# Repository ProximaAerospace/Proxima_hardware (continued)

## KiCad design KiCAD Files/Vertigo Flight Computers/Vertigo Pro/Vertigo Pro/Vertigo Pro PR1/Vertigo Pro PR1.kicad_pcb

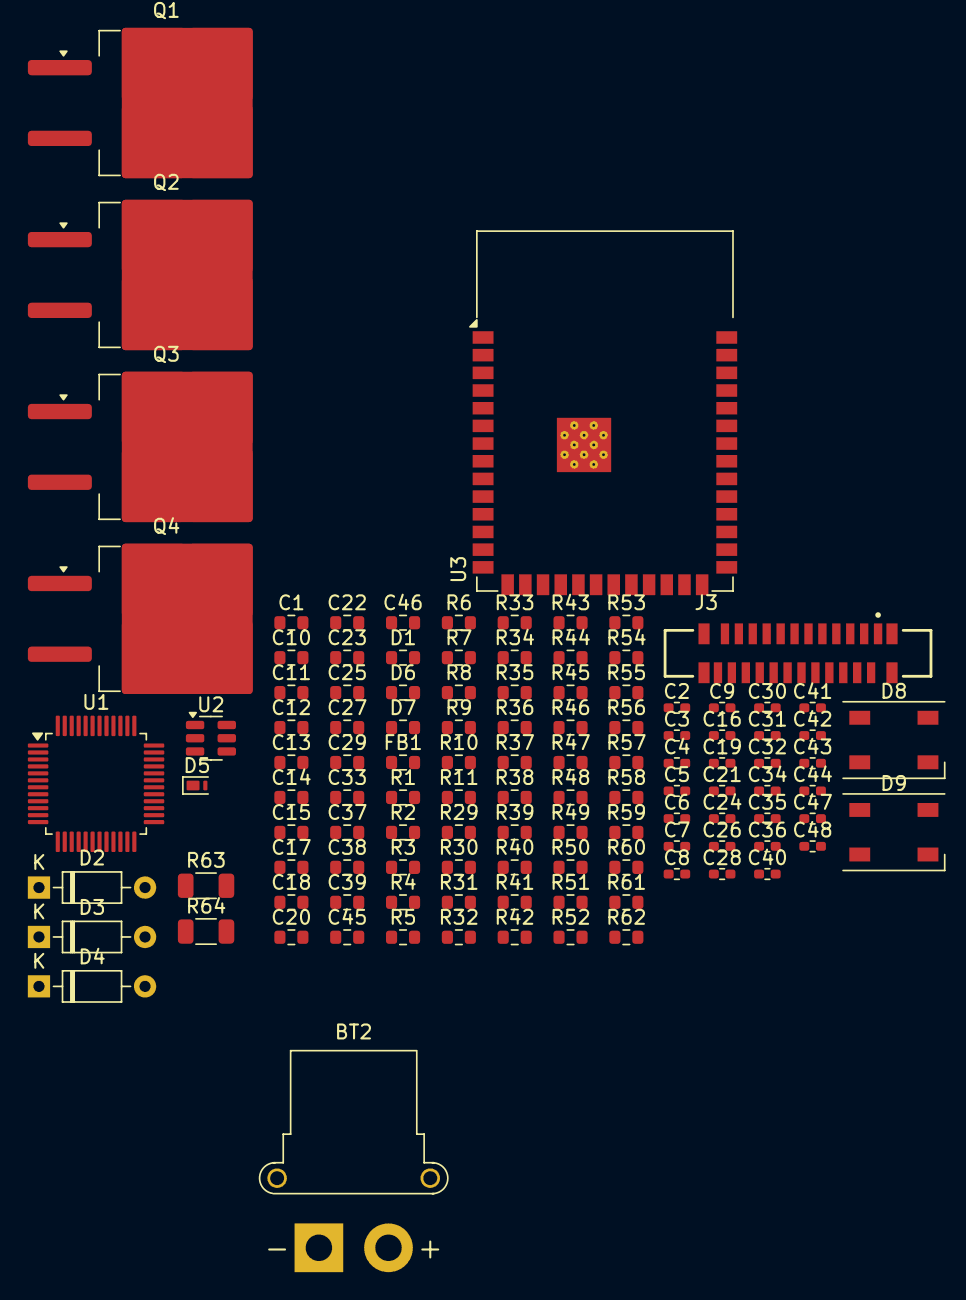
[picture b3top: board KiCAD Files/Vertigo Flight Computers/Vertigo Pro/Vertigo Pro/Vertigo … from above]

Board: 4 copper layers, 114 parts (0 on the bottom side), 68 nets, no tracks yet.

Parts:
BT2: 3S LiPo; AMASS_XT30PW-F_1x02_P2.50mm_Horizontal
C1, C12, C17, C23, C25, C27, C29: 10uF; R_0603_1608Metric
C2, C4, C6, C7, C8, C35, C36: 100nF; R_0402_1005Metric_Pad0.72x0.64mm_HandSolder
C3, C5: 10pF; R_0402_1005Metric_Pad0.72x0.64mm_HandSolder
C9, C31: 10nF; R_0402_1005Metric_Pad0.72x0.64mm_HandSolder
C10, C11, C39: 1uF; R_0603_1608Metric
C13: 100nF; R_0603_1608Metric
C14, C15: 22uF; R_0603_1608Metric
C16, C19, C21, C24, C26, C28, C30, C32, C34, C40, C41, C43, C44, C47: 0.1uF; R_0402_1005Metric_Pad0.72x0.64mm_HandSolder
C18, C20, C22, C45, C46: 4.7uF; R_0603_1608Metric
C33, C37, C38: 2.2uF; R_0603_1608Metric
C42, C48: 0.47uF; R_0402_1005Metric_Pad0.72x0.64mm_HandSolder
D1, D6: LED; R_0603_1608Metric
D2, D3, D4: 1N4148; D_DO-35_SOD27_P7.62mm_Horizontal
D5: uClamp0571P; Nexperia_DSN1608-2_1.6x0.8mm
D7: D; R_0603_1608Metric
D8, D9: SK6812; LED_SK6812_PLCC4_5.0x5.0mm_P3.2mm
FB1: 120R; R_0603_1608Metric
J3: FFC2A32-24-T; GCT_FFC2A32-24-T
Q1, Q2, Q3, Q4: IRF530SPBF; TO-263-2
R1, R9, R10, R29, R30, R31, R32, R33: 10K; R_0603_1608Metric
R2, R3, R44: 22R; R_0603_1608Metric
R4, R5: 5.1k; R_0603_1608Metric
R6: 3k; R_0603_1608Metric
R7, R8: 1K; R_0603_1608Metric
R11, R43, R45, R46, R49, R51, R52, R55, R56, R57, R58: 1k; R_0603_1608Metric
R34: 18.2k; R_0603_1608Metric
R35, R37, R39, R41: 5k; R_0603_1608Metric
R36: 64.4k; R_0603_1608Metric
R38: 23.7k; R_0603_1608Metric
R40: 10.2k; R_0603_1608Metric
R42: 21.5k; R_0603_1608Metric
R47, R53, R59, R60: 10k; R_0603_1608Metric
R48: 1.5k; R_0603_1608Metric
R50, R54, R61, R62: 3.44k; R_0603_1608Metric
R63, R64: 470R; R_1206_3216Metric
U1: STM32F103C8Tx; LQFP-48_7x7mm_P0.5mm
U2: AP63203WU; TSOT-23-6
U3: ESP32-S3-WROOM-1

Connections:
+3.3V: C1.1, C4.1, C6.1, C7.1, C8.1, C11.1, C14.1, C15.1, C16.2, C17.2, C23.2, C24.1, C27.2, C28.1, C31.2, C32.2, C33.2, C35.2, C36.1, C37.1, C38.2, FB1.2, R7.2, R29.2, R30.2, R31.2, R32.2, R33.2, U1.1 (VBAT), U1.24 (VDD), U1.36 (VDD), U1.48 (VDD), U2.1 (FB), U3.2 (3V3)
+3.3VA: C9.1, C10.1, FB1.1, U1.9 (VDDA)
/5V_USB_RAW: D5.1 (K), R38.2, R40.2
/ALED_PWR: C48.2, D8.3 (VDD), D9.3 (VDD)
/BATT_OUT: R6.1, R34.2, R36.2
/BATT_U: R6.2, R11.1, U1.18 (PB0)
/BOOT0: R1.2, U1.44 (BOOT0)
/CAM_PWDN: J3.8, R10.1
/CAM_RESET: J3.6, R9.2
/CONTI_C1: R50.1, R51.2, U1.14 (PA4)
/CONTI_C2: R49.2, R54.1
/CONTI_C3: R55.2, R61.1
/CONTI_C4: R56.2, R62.1
/DOVDD_2V8: C20.2, C21.2, C22.2, C25.2, C26.1, J3.11, R9.1
/DVDD_1V5: C18.2, C19.2, C29.2, C30.1, J3.10
/DVP_HREF: J3.9, U3.7 (IO7)
/DVP_PCLK: J3.17, U3.21 (IO13)
/DVP_VSYNC: J3.3, J3.7, U3.4 (IO4)
/DVP_Y2: J3.19, U3.19 (IO11)
/DVP_Y3: J3.21, U3.17 (IO9)
/DVP_Y4: J3.22, U3.12 (IO8)
/DVP_Y5: J3.20, U3.18 (IO10)
/DVP_Y6: J3.18, U3.20 (IO12)
/DVP_Y7: J3.16, U3.11 (IO18)
/DVP_Y8: J3.14, U3.10 (IO17)
/DVP_Y9: J3.12, U3.9 (IO16)
/ESP_I2C_SCL: J3.5, U3.5 (IO5)
/HSE_IN: C3.1, U1.5 (PD0)
/HSE_OUT: C5.1, U1.6 (PD1)
/IGN_1: R46.1, U1.10 (PA0)
/IGN_2: R52.1, U1.11 (PA1)
/IGN_3: R57.1, U1.12 (PA2)
/IGN_4: R58.1, U1.13 (PA3)
/IO15: J3.13, U3.8 (IO15)
/NRST: C2.1, U1.7 (NRST)
/PWR_MUX: C12.1, C41.2, C47.2, U2.2 (EN), U2.3 (IN)
/STM_ALED: R63.1, U1.4 (PC15)
/STM_I2C_SCL: R29.1, U1.21 (PB10)
/STM_I2C_SDA: R30.1, U1.22 (PB11)
/ULN_3V3: C45.2, C46.2, D7.2 (A), R48.2
/USB_D+: R2.2, U1.33 (PA12)
/USB_D-: R3.1, U1.32 (PA11)
AGND: BT2.2 (-), C1.2, C2.2, C3.2, C4.2, C5.2, C6.2, C7.2, C8.2, C9.2, C10.2, C11.2, C12.2, C14.2, C15.2, C16.1, C17.1, C18.1, C19.1, C20.1, C21.1, C22.1, C23.1, C24.2, C25.1, C26.2, C27.1, C28.2, C29.1, C30.2, C31.1, C32.1, C33.1, C34.2, C35.1, C36.2, C37.2, C38.1, C39.2, C40.1, C41.1, C42.1, C43.1, C44.1, C45.1, C46.1, C47.1, C48.1, D1.1 (K), D5.2 (A), D6.1 (K), D8.1 (VSS), D9.1 (VSS), J3.2, J3.15, Q1.3 (S), Q2.3 (S), Q3.3 (S), Q4.3 (S), R4.1, R5.1, R10.2, R11.2, R35.1, R37.2, R39.1, R41.1, R42.1, R47.1, R49.1, R51.1, R53.1, R55.1, R56.1, R59.1, R60.1, U1.8 (VSSA), U1.23 (VSS), U1.35 (VSS), U1.47 (VSS), U2.4 (GND), U3.1 (GND), U3.40 (GND), U3.41 (GND)
unnamed: D1.2 (A), R7.1, R8.1
unnamed: D2.2 (A), R31.1
unnamed: D3.2 (A), R32.1
unnamed: D4.2 (A), R33.1
unnamed: D6.2 (A), R43.2
unnamed: D7.1 (K), R45.2
unnamed: D8.2 (DIN), R63.2
unnamed: D9.2 (DIN), R64.2
unnamed: R2.1, R48.1
unnamed: Q1.2 (D), R50.2
unnamed: Q2.2 (D), R54.2
unnamed: Q3.2 (D), R61.2
unnamed: Q4.2 (D), R62.2
unnamed: Q1.1 (G), R46.2, R47.2
unnamed: Q2.1 (G), R52.2, R53.2
unnamed: Q3.1 (G), R57.2, R59.2
unnamed: Q4.1 (G), R58.2, R60.2
unnamed: C13.1, U2.6 (BST)
unnamed: C13.2, U2.5 (SW)
unnamed: R8.2, U3.15 (IO3)
unnamed: R40.1, R41.2
unnamed: R36.1, R37.1
unnamed: R38.1, R39.2
unnamed: R34.1, R35.2
unnamed: C42.2, C43.2

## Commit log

2024-06-12 Create n-a
2024-06-13 Create test
2024-06-13 Nothing important
2024-06-14 Work
2024-06-14 Error fix
2024-06-16 8.0.3 kicad
2024-06-16 Page size
2024-06-16 Page size 2
2024-06-16 kicad libraries folder
2024-06-16 footpirnts
2024-06-16 Sch & ftp
2024-06-16 test
2024-06-16 cosm
2024-06-16 cosm2
2024-06-18 footprinty
2024-06-18 New 2.8V cam voltage reg
2024-06-18 1.5V new cam voltage ldo
2024-06-18 ESP Circuit fix
2024-06-18 Bootloader mode selection
2024-06-18 Create LICENSE
2024-06-18 Annotations, footprints etc.
2024-06-18 something
2024-06-19 footprint
2024-06-19 footprint 2
2024-06-19 New reverse polarity protection on PMOSFET
2024-06-19 Remove Zener
2024-06-20 New pyro circuitry
2024-06-20 Flash fix
2024-06-20 ULN Reg to sensors
2024-06-20 Power LEDs for uCs + fix
2024-06-23 Pyro fix, est
2024-06-23 High G-force IMU added, Low G-force IMU fix, added more annotations
2024-06-23 Removed flash IC
2024-06-23 High-G IMU fix
2024-06-24 Sch fix
2024-06-24 LiPo/USB protection fix
2024-06-26 Footprints, GPS fix
2024-06-26 Schematic fix
2024-06-27 New pyro MOSFETs, sch fix, adn
2024-06-27 prepcb
2024-06-27 redo
2024-06-28 Sch fix, prepcb
2024-06-28 pcb fix
2024-06-29 Switching voltage regulator layout
2024-06-29 cu fix
2024-07-06 MuCU dcaps, crystal, status led etc
2024-07-08 3D, caps, syme, pyro circ & usb fix
2024-07-08 Cam cap, crystal, pyro, led
2024-07-08 Est, remove pi filter
2024-07-08 USB Diff pair
2024-07-08 Est, rounded edges
2024-07-08 info
2024-07-09 kamera ogarnięta
2024-07-09 GPS Layout, Cam circuitry Layout, est and other stuff
2024-07-09 IMU, Baro decoupling caps
2024-07-09 Input mosfet circuitry, ULN, ALED + Cam reg, USB CC pins
2024-07-09 MuCU crystal circuitry
2024-07-09 Flash, pre testpoint, est, other boring stuff
2024-07-09 Schematic fix, aled signal testpoint
2024-07-09 Test point, sch, com fix + other stuff
2024-07-10 Schematic and PCB edit
    - USB Circuitry
    - I2C Communication
    - New pyro mosfets
2024-07-10 PCB Edit
    - ALED power routing
    - Esthetics
    - Signal traces routing
2024-07-10 Schematic and PCB edit
    - Enabled second UART for MuCU
    - Routed some stuff
    - Schematic fix
2024-07-10 New pyro channel circuitry routed, logo and text + est
2024-07-10 Pyro and other stuff
2024-07-10 VIN and pyro routing
2024-07-10 Power traces, pyro
2024-07-11 New pyro mosfet, routing, est, sch edit
2024-07-11 Many fixes, STM ALED double pin fix, cam and aled reg moved, etc
2024-07-11 ULN Moved, ALED, est - all parts on the board!
2024-07-11 Two-stage ULN
2024-07-11 Power routing
2024-07-11 swd routing fix
2024-07-12 Much routing
2024-07-12 Routing, EEPROM power fix + other stuff
2024-07-12 Routing
2024-07-14 USB Diode fix
2024-07-18 poprawki by marcin
2024-07-18 Silkscreen
2024-07-18 UART2
2024-07-18 Silk fix
2024-07-18 Via fix + UART
2024-07-18 Via fix, est
2024-07-18 internal layers clean
2024-07-19 BATT_U trace fix, est, via fix
2024-07-19 Routing fix
2024-07-19 Via fix, esthetics ULN, 1V5 and 2V8 test point removed
2024-07-19 esthetics
2024-07-19 UART2 testpoint, silkscreen, SWD desc, esthetics + minor fixes
2024-07-19 UART2 routing, traces fix
2024-07-19 ULN First stage IC 3D Model, ALED testpoint moved
2024-07-19 Silkscreen fix
2024-07-19 via fix again (piece of shit)
2024-07-19 i2c plus niepodłączone elementy
2024-07-19 Silkscreen fix, est
2024-07-19 Routing fix, via fix, silkscreen
2024-07-19 via fix
2024-07-19 0402 cap to 0603, via fix, routing
2024-07-19 few fix
2024-07-20 GND Vias, silkscreen fix, routing fix
2024-07-20 DRC, Silkscreen fix
2024-07-20 GND Vias, DRC
2024-07-22 GND Via, RF 0603, USB fix (via, TVS), routing fix
2024-07-22 aled fix
2024-07-22 uart and 3v3 fix
2024-07-22 GPS dcaps, routing fix
2024-07-22 Caps, routing fix
2024-07-22 Silk +-fix, routing fix
2024-07-22 DRC, silk, routing
2024-07-23 DRC, Routing fix
2024-07-23 UART1/2 fix + routing
2024-07-23 Gerbers, last fix
2024-07-25 GRB, BOM
2024-11-04 Created Vertigo Daughterboard R1
2024-11-04 PCB, Sensors, Pins etc
2024-11-06 switched I2C to SPI, new PCB shape, fix for BOM
2024-11-06 note
2024-11-06 note 2
